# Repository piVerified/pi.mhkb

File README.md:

# pi.mhkb

Introducing pi.mhkb, a completely custom made HHKB style mechanical keyboard

---
# Features

1. Full HHKB layout with custom key mapping
2. Custom PCB designed in KiCAD
3. 3D printed case designed in Fusion 360

## Fusion 360

### 1. Case

| Top | Side |
| :-: | :--: |
|  | |

---
## KiCAD

| Schematic |
| :-------: |
||
| PCB |
|  |

---
.png)
#BOM
| Name | Purpose | Quantity | Total Cost (USD) | Distributor |
| :--- | :--- | ---: | ---: | :--- |
| PCB | the Brain | 1 | 37.94 | Robu |
| keycaps | covering the keys | 1 | 14.02 | curiosity caps |
| usb cable | for connecting and debugging | 1 | 1.72 | Amazon |
| keyboard Case | Enclousere of the system | 1 | 5.00 | #printinglegion |
| knob | for rotatory knob | 1 | 3.86 | Curiosity Caps |
| Stabilizers (set) | for the biggerkeys stability | 1 | 9.37 | KEEBSMOD |
| Gateron milky yellow | typing | 7 | 14.00 | Meckeys |
| Hotswap Sockets (set of 10) | to make it hotswapable | 7 | 5.81 | Mecheys |
| M3x4 mm Brass Heat Set Threaded Round Insert Nut (x25) | for housing screws | 1 | 0.98 | Robu |
| Raspberry Pi Pico WH | the main controller | 1 | 5.50 | Robu |
| 1N4148 1W Zener Diode | to prevent ghosting of keys | 70 | 0.70 | Robu |

---
# Softwares Used

* KiCAD -> PCB Design
* Fusion 360 -> Case design
* Blender -> Cover Image

---
# Bibliography

> This project would not have been possible without the help of the amazing people of the internet and the Hack Club community.

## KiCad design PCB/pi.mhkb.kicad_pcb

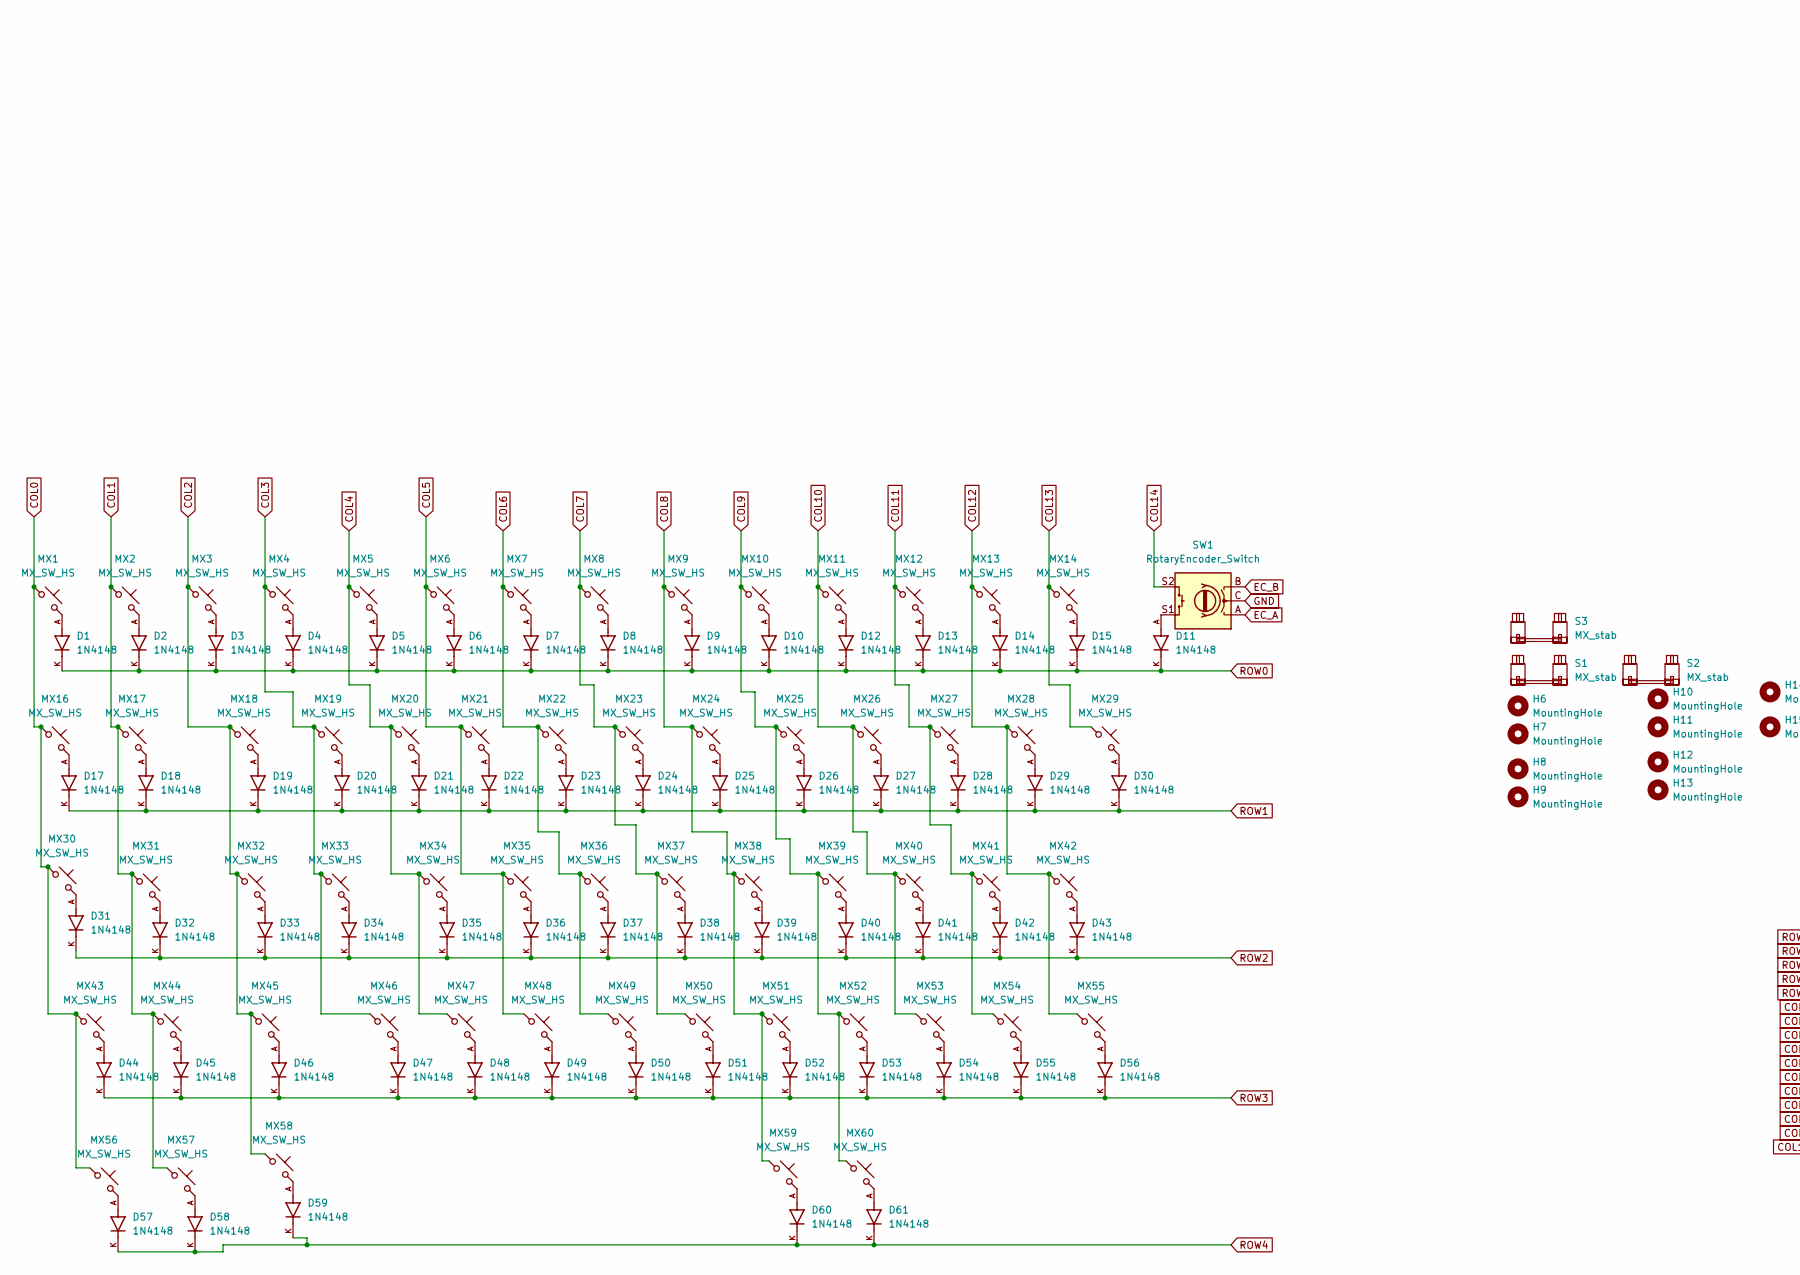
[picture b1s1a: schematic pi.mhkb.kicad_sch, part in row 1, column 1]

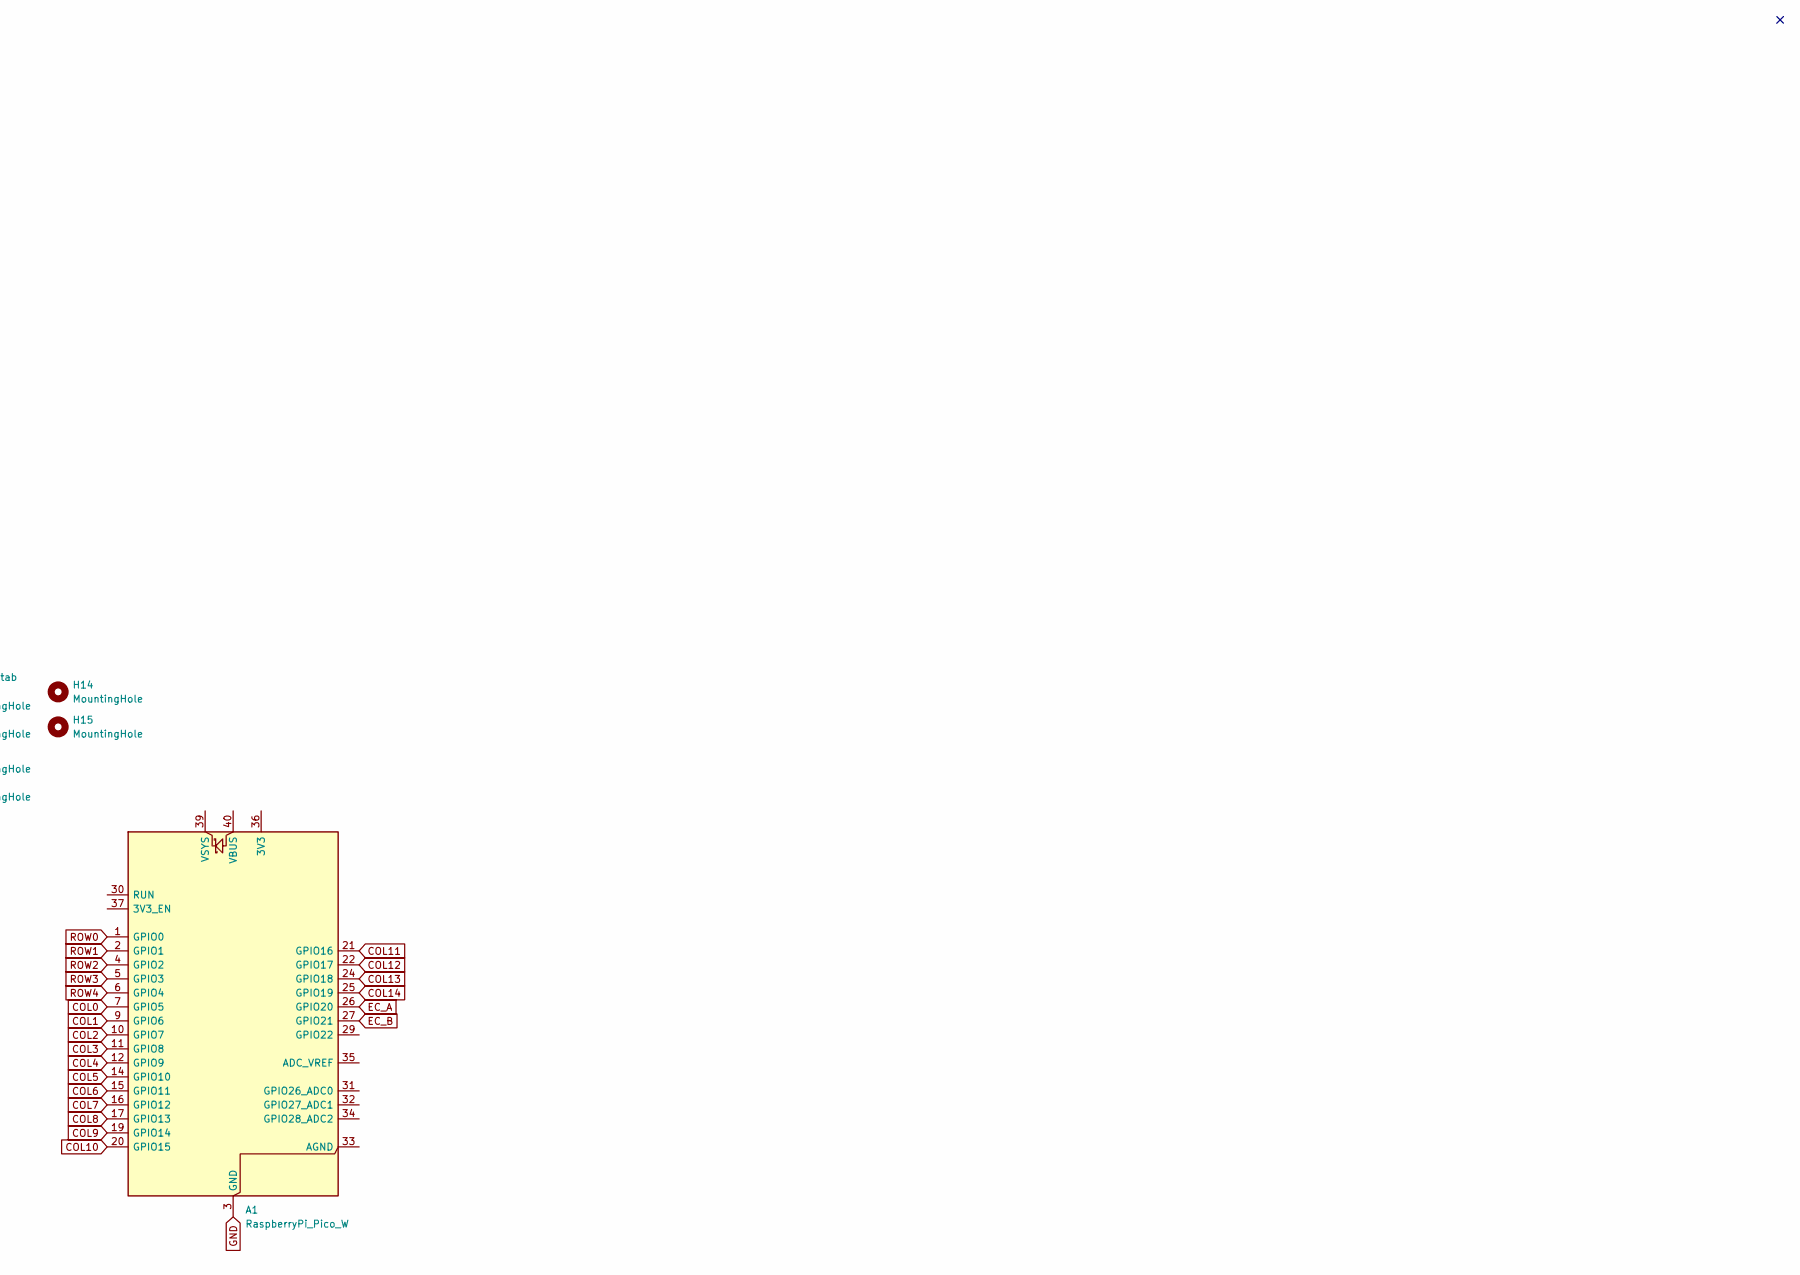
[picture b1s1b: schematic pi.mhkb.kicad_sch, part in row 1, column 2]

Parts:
A1: RaspberryPi_Pico_W; RaspberryPi_Pico_W_SMD_HandSolder
D1, D2, D3, D4, D5, D6, D7, D8, D9, D10, D11, D12, D13, D14, D15, D17, D18, D19, D20, D21, D22, D23, D24, D25, D26, D27, D28, D29, D30, D31, D32, D33, D34, D35, D36, D37, D38, D39, D40, D41, D42, D43, D44, D45, D46, D47, D48, D49, D50, D51, D52, D53, D54, D55, D56, D57, D58, D59, D60, D61: 1N4148; DIODE-1N4148; PARTREV 5
H6, H7, H8, H9, H10, H11, H12, H13, H14, H15: MountingHole; MountingHole_3.2mm_M3
MX1, MX2, MX3, MX4, MX5, MX6, MX7, MX8, MX9, MX10, MX11, MX12, MX13, MX14, MX16, MX17, MX18, MX19, MX20, MX21, MX22, MX23, MX24, MX25, MX26, MX27, MX28, MX29, MX30, MX31, MX32, MX33, MX34, MX35, MX36, MX37, MX38, MX39, MX40, MX41, MX42, MX43, MX44, MX45, MX46, MX47, MX48, MX49, MX50, MX51, MX52, MX53, MX54, MX55, MX56, MX57, MX58, MX59, MX60: MX_SW_HS; SW_Hotswap_Kailh_MX_1.00u
S1, S2: MX_stab; STAB_MX_P_2.25u
S3: MX_stab; Stabilizer_Cherry_MX_6.25u
SW1: RotaryEncoder_Switch; RotaryEncoder_Alps_EC11E-Switch_Vertical_H20mm

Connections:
COL0: A1.7 (GPIO5), MX1.1, MX16.1, MX30.1, MX43.1, MX56.1
COL1: A1.9 (GPIO6), MX2.1, MX17.1, MX31.1, MX44.1, MX57.1
COL2: A1.10 (GPIO7), MX3.1, MX18.1, MX32.1, MX45.1, MX58.1
COL3: A1.11 (GPIO8), MX4.1, MX19.1, MX33.1, MX46.1
COL4: A1.12 (GPIO9), MX5.1, MX20.1, MX34.1, MX47.1
COL5: A1.14 (GPIO10), MX6.1, MX21.1, MX35.1, MX48.1
COL6: A1.15 (GPIO11), MX7.1, MX22.1, MX36.1, MX49.1
COL7: A1.16 (GPIO12), MX8.1, MX23.1, MX37.1, MX50.1
COL8: A1.17 (GPIO13), MX9.1, MX24.1, MX38.1, MX51.1, MX59.1
COL9: A1.19 (GPIO14), MX10.1, MX25.1, MX39.1, MX52.1, MX60.1
COL10: A1.20 (GPIO15), MX11.1, MX26.1, MX40.1, MX53.1
COL11: A1.21 (GPIO16), MX12.1, MX27.1, MX41.1, MX54.1
COL12: A1.22 (GPIO17), MX13.1, MX28.1, MX42.1, MX55.1
COL13: A1.24 (GPIO18), MX14.1, MX29.1
COL14: A1.25 (GPIO19), SW1.S2
EC_A: A1.26 (GPIO20), SW1.A
EC_B: A1.27 (GPIO21), SW1.B
GND: A1.3 (GND), A1.8 (GND), A1.13 (GND), A1.18 (GND), A1.23 (GND), A1.28 (GND), A1.38 (GND), SW1.C
unnamed: D1.A, MX1.2
unnamed: D2.A, MX2.2
unnamed: D3.A, MX3.2
unnamed: D4.A, MX4.2
unnamed: D5.A, MX5.2
unnamed: D6.A, MX6.2
unnamed: D7.A, MX7.2
unnamed: D8.A, MX8.2
unnamed: D9.A, MX9.2
unnamed: D10.A, MX10.2
unnamed: D11.A, SW1.S1
unnamed: D12.A, MX11.2
unnamed: D13.A, MX12.2
unnamed: D14.A, MX13.2
unnamed: D15.A, MX14.2
unnamed: D17.A, MX16.2
unnamed: D18.A, MX17.2
unnamed: D19.A, MX18.2
unnamed: D20.A, MX19.2
unnamed: D21.A, MX20.2
unnamed: D22.A, MX21.2
unnamed: D23.A, MX22.2
unnamed: D24.A, MX23.2
unnamed: D25.A, MX24.2
unnamed: D26.A, MX25.2
unnamed: D27.A, MX26.2
unnamed: D28.A, MX27.2
unnamed: D29.A, MX28.2
unnamed: D30.A, MX29.2
unnamed: D31.A, MX30.2
unnamed: D32.A, MX31.2
unnamed: D33.A, MX32.2
unnamed: D34.A, MX33.2
unnamed: D35.A, MX34.2
unnamed: D36.A, MX35.2
unnamed: D37.A, MX36.2
unnamed: D38.A, MX37.2
unnamed: D39.A, MX38.2
unnamed: D40.A, MX39.2
unnamed: D41.A, MX40.2
unnamed: D42.A, MX41.2
unnamed: D43.A, MX42.2
unnamed: D44.A, MX43.2
unnamed: D45.A, MX44.2
unnamed: D46.A, MX45.2
unnamed: D47.A, MX46.2
unnamed: D48.A, MX47.2
unnamed: D49.A, MX48.2
unnamed: D50.A, MX49.2
unnamed: D51.A, MX50.2
unnamed: D52.A, MX51.2
unnamed: D53.A, MX52.2
unnamed: D54.A, MX53.2
unnamed: D55.A, MX54.2
unnamed: D56.A, MX55.2
unnamed: D57.A, MX56.2
unnamed: D58.A, MX57.2
unnamed: D59.A, MX58.2
unnamed: D60.A, MX59.2
unnamed: D61.A, MX60.2
ROW0: A1.1 (GPIO0), D1.K, D2.K, D3.K, D4.K, D5.K, D6.K, D7.K, D8.K, D9.K, D10.K, D11.K, D12.K, D13.K, D14.K, D15.K
ROW1: A1.2 (GPIO1), D17.K, D18.K, D19.K, D20.K, D21.K, D22.K, D23.K, D24.K, D25.K, D26.K, D27.K, D28.K, D29.K, D30.K
ROW2: A1.4 (GPIO2), D31.K, D32.K, D33.K, D34.K, D35.K, D36.K, D37.K, D38.K, D39.K, D40.K, D41.K, D42.K, D43.K
ROW3: A1.5 (GPIO3), D44.K, D45.K, D46.K, D47.K, D48.K, D49.K, D50.K, D51.K, D52.K, D53.K, D54.K, D55.K, D56.K
ROW4: A1.6 (GPIO4), D57.K, D58.K, D59.K, D60.K, D61.K

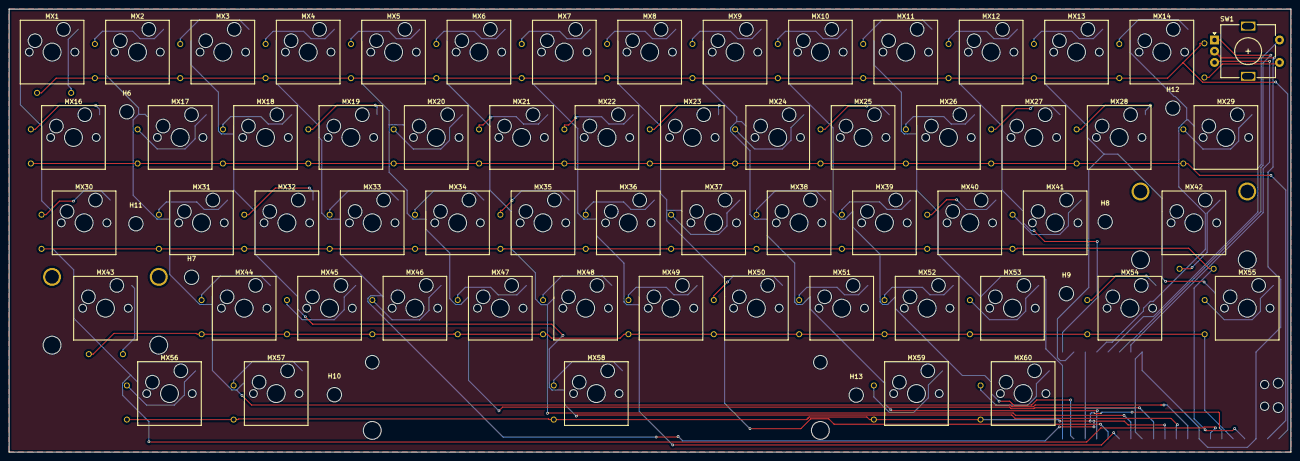
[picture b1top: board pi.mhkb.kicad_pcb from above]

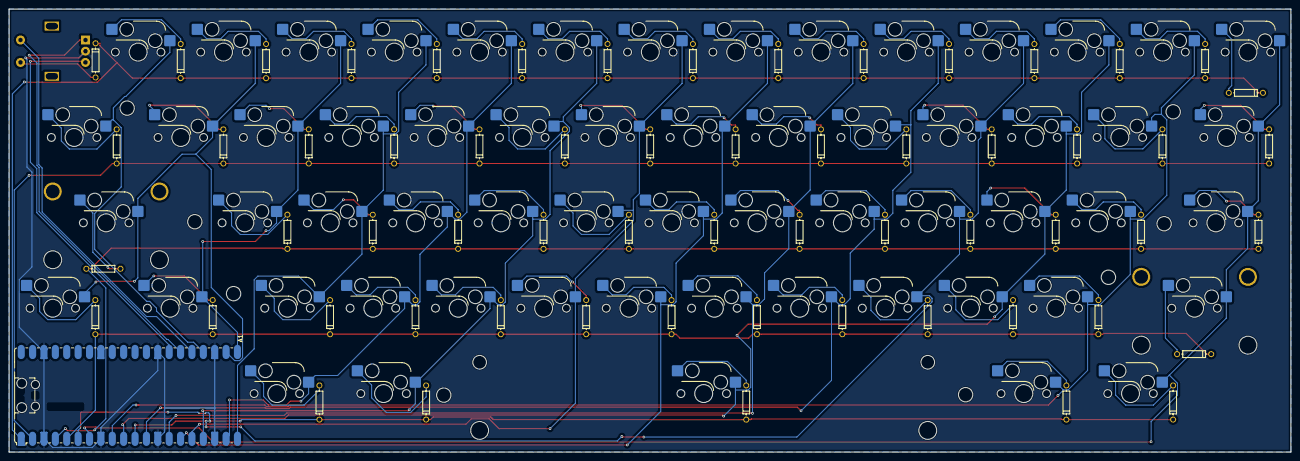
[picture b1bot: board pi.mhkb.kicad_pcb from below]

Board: 2 copper layers, 286.1 x 98.9 mm, 132 parts (61 on the bottom side), 83 nets.

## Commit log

2026-02-14 Rename project from pi.hhkb to pi.mhkb
2026-02-24 Initial plan
2026-02-24 Structure repo similarly to pi.keeb
2026-02-24 Update README: Modify features and software used
    Removed BOM section and added Blender to software list.
2026-04-03 Update README with images for case and KiCAD
    Added images to README for keyboard case, schematic, and PCB.
2026-04-03 Add BOM section and wireframe image to README
2026-04-03 Add main.py for keyboard firmware configuration
